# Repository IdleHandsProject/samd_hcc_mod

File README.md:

# SAMD21 HCC Module

Check out the Kickstarter for the HCC Module!

[HCC Mod Kickstarter](https://www.kickstarter.com/projects/idlehandsdev/hcc-mod-ready-to-solder-arduino-module)

An easy to solder Arduino and CircuitPython compatible surface mount module aimed to bridge the gap between using "off the shelf" microcontrollers to creating custom PCBs. 
The module will come with a standard USB enabled Arduino bootloader.

## Arduino IDE Install

Inside of the folder "BOOTLOADER" there is a folder called "IdleHandsDev". Once you download or clone the repo, take the IdleHandsDev folder and place it in the "hardware" folder found within your default Arduino folder. This will allow you to select the HCC Module in the Arduino IDE. You can also use "Arduino/Genuino Zero (Native USB). It will have the same pinout.

## Videos

## Demo Boards

### Cherry MX Board

### MOD_BOY - Arduino Gaming Device and Gaming Controller

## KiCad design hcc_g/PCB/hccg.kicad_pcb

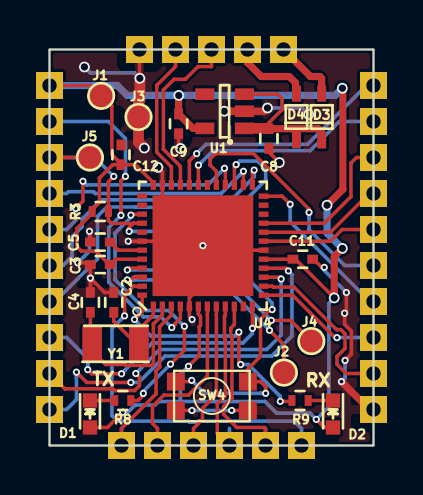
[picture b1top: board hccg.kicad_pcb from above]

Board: 2 copper layers, 18.0 x 22.0 mm, 25 parts (0 on the bottom side), 40 nets.

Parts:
C2, C4: 15pF; C_0402
C3, C5, C11, C12: 0.1uF; C_0402
C8, C9: 1uF; C_0402
D1: GLED; LED-0603
D2: YLED; LED-0603
D3, D4: BAT20J; SOD-323
J1, J2, J3, J4, J5: TEST_1P; TESTP_1_5
R3: 10k; R_0402
R8, R9: 1k; R_0402
SW4: SW_PUSH; switch_kmr2
U1: AP2112K-3.3V; SOT-23-5
U2: SAMD21G18; QFN-48-EP-ST_NoVia
U4: SAMD21_MOD; SAMD21G18_MOD
Y1: Crystal_Small; crystal_smd_3.20x1.50mm2

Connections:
+3V3: C3.1, C9.1, C11.1, C12.1, D1.2, D2.2, J1.1, R3.1, U1.5, U2.6, U2.17, U2.36, U2.44, U4.1
+BATT: D3.2, U4.27
A0/DAC: U2.3, U4.11
A1: U2.7, U4.12
A2: U2.8, U4.13
A3: U2.9, U4.14
A4: U2.10, U4.15
A5: U2.47, U4.16
AREF: U2.4, U4.2
CLK: U2.20, U4.23
D3: U2.14, U4.18
D4: U2.13, U4.19
D5: U2.24, U4.20
D6: U2.29, U4.21
D9: U2.12, U4.8
D10: U2.27, U4.7
D11: U2.25, U4.6
D12: U2.28, U4.5
D13: U2.26, U4.4
GND: C2.2, C3.2, C4.2, C5.2, C8.2, C9.2, C11.2, C12.2, J3.1, SW4.2, U1.2, U2.5, U2.18, U2.35, U2.42, U4.17, U4.31
MISO: U2.21, U4.24
MOSI: U2.19, U4.22
unnamed: C2.1, U2.1, Y1.2
unnamed: C4.1, U2.2, Y1.1
unnamed: C5.1, U2.43
unnamed: C8.1, D3.1, D4.1, U1.1, U1.3
unnamed: D1.1, R8.2
unnamed: D2.1, R9.2
RESET: J5.1, R3.2, SW4.1, U2.40, U4.3
RX/D0: U2.16, U4.10
RXLED: R9.1, U2.48
SCL: U2.32, U4.26
SDA: U2.31, U4.25
SWCLK: J4.1, U2.45
SWDIO: J2.1, U2.46
TX/D1: U2.15, U4.9
TXLED: R8.1, U2.39
USB_D+: U2.34, U4.30
USB_D-: U2.33, U4.29
VBUS: D4.2, U4.28

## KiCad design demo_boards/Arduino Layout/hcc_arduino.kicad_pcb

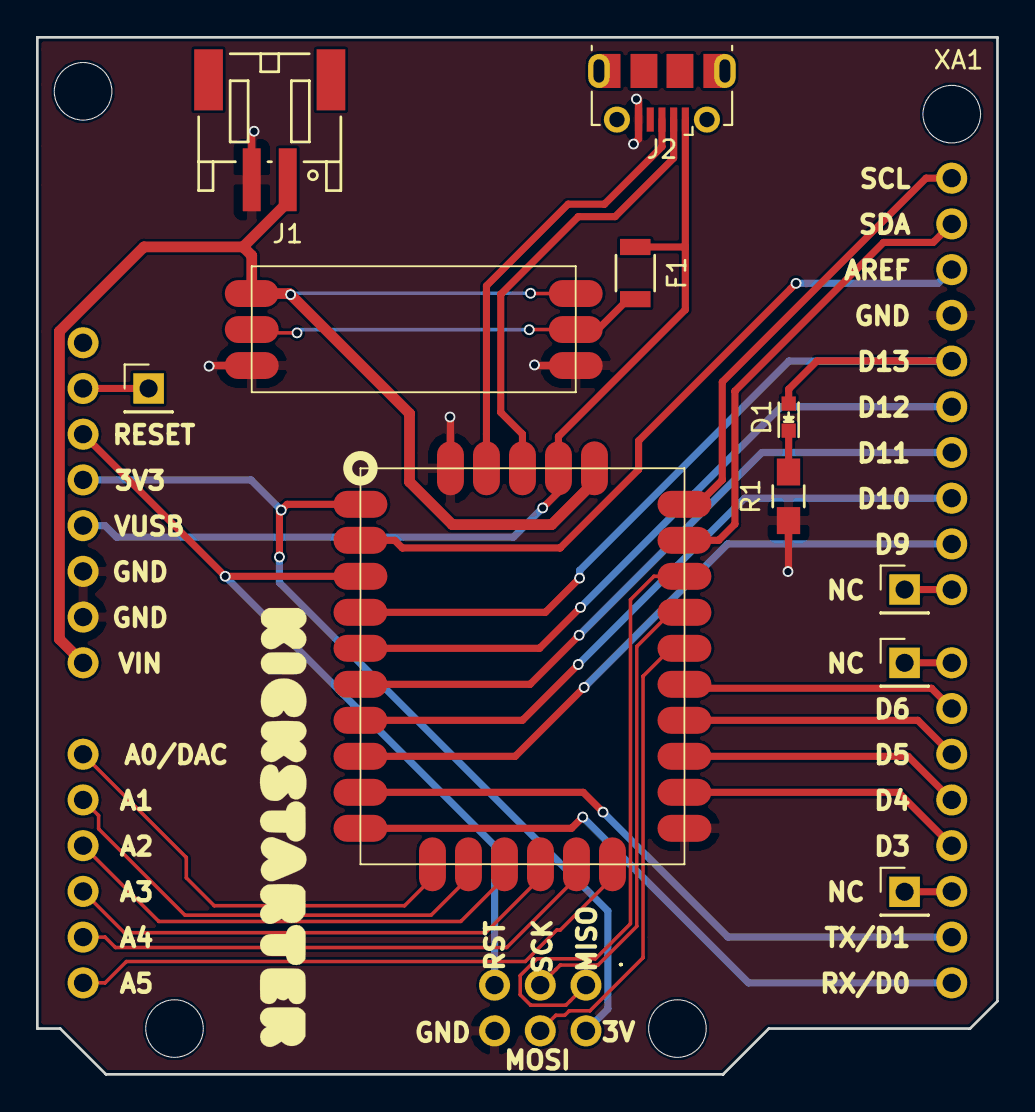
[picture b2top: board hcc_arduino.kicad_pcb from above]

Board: 2 copper layers, 53.3 x 57.6 mm, 12 parts (0 on the bottom side), 36 nets.

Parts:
D1: LED; LED-0603
F1: Fuse; R_1206
J1: BATT; Connectors_JST_S2B-PH-SM4-TB
J2: USB_OTG; USB_Micro-B_Molex-105017-0001
J3: D2; Pin_Header_Straight_1x01_Pitch2.54mm
J4: D7; Pin_Header_Straight_1x01_Pitch2.54mm
J5: D8; Pin_Header_Straight_1x01_Pitch2.54mm
J6: IOREF; Pin_Header_Straight_1x01_Pitch2.54mm
R1: 2k; R_0805_HandSoldering
U1: SAMD21_MOD; SAMD_HCC_G_FOOT
U2: charge_mod; LIPO_CHARGE_MOD_FOOTPRINT
XA1: Arduino_M0_Shield; Arduino_HCC

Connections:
+3V3: U1.1, XA1.3V3, XA1.5V2
+BATT: J1.1, U1.27, U2.1, XA1.VIN
A0/DAC: U1.11, XA1.A0
A1: U1.12, XA1.A1
A2: U1.13, XA1.A2
A3: U1.14, XA1.A3
A4: U1.15, XA1.A4
A5: U1.16, XA1.A5
AREF: U1.2, XA1.AREF
CLK: U1.23, XA1.SCK
D3: U1.18, XA1.D3
D4: U1.19, XA1.D4
D5: U1.20, XA1.D5
D6: U1.21, XA1.D6
D9: U1.8, XA1.D9
D10: U1.7, XA1.D10
D11: U1.6, XA1.D11
D12: U1.5, XA1.D12
D13: D1.2, U1.4, XA1.D13
GND: J1.2, J2.5, R1.1, U1.17, U1.31, U2.3, XA1.GND1, XA1.GND2, XA1.GND3, XA1.GND4
MISO: U1.24, XA1.MISO
MOSI: U1.22, XA1.MOSI
unnamed: D1.1, R1.2
unnamed: F1.2, U2.2
unnamed: J2.2, U1.29
unnamed: J2.3, U1.30
unnamed: J3.1, XA1.D2
unnamed: J4.1, XA1.D7
unnamed: J5.1, XA1.D8
unnamed: J6.1, XA1.IORF
RESET: U1.3, XA1.RST1, XA1.RST2
RX/D0: U1.10, XA1.D0
SCL: U1.26, XA1.SCL
SDA: U1.25, XA1.SDA
TX/D1: U1.9, XA1.D1
VBUS: F1.1, J2.1, U1.28, XA1.5V1

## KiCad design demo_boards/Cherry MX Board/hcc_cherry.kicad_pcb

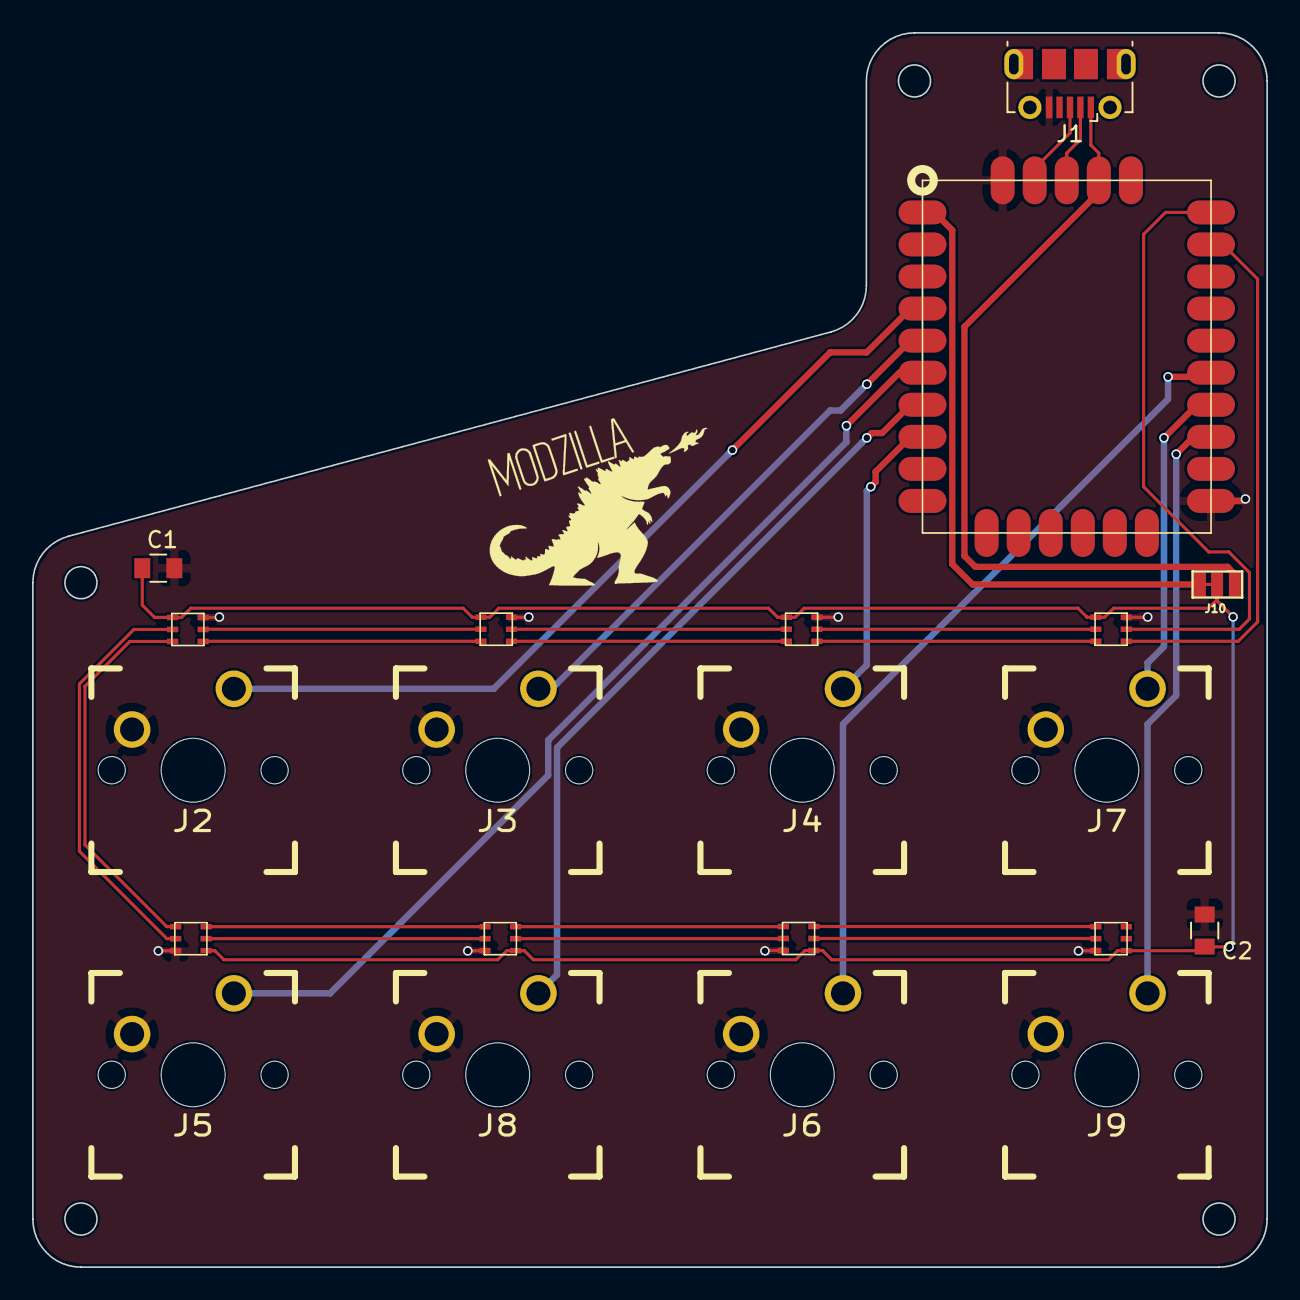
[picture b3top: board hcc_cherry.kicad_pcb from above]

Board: 2 copper layers, 77.0 x 77.0 mm, 21 parts (0 on the bottom side), 29 nets.

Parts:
C1, C2: 1uF; C_0805
J1: USB_OTG; USB_Micro-B_Molex-105017-0001
J2: SW1; CHERRY_PCB_100H
J3: SW2; CHERRY_PCB_100H
J4: SW3; CHERRY_PCB_100H
J5: SW4; CHERRY_PCB_100H
J6: SW5; CHERRY_PCB_100H
J7: SW6; CHERRY_PCB_100H
J8: SW7; CHERRY_PCB_100H
J9: SW8; CHERRY_PCB_100H
J10: GS3; 3WAY_JUMPER_SMD
U1, U2, U3, U5, U6, U7, U8, U9: APA102; APA102-2020_AFSTYLE
U4: SAMD21_MOD; SAMD_HCC_G_FOOT

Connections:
+3V3: C1.1, C2.1, J10.2, J10.3, U1.1, U2.1, U3.1, U4.1, U5.1, U6.1, U7.1, U8.1, U9.1
CKI: U1.5, U4.26
D4: J9.1, U4.19
D5: J7.1, U4.20
D6: J6.1, U4.21
D9: J4.1, U4.8
D10: J8.1, U4.7
D11: J5.1, U4.6
D12: J3.1, U4.5
D13: J2.1, U4.4
GND: C1.2, C2.2, J1.5, J2.2, J3.2, J4.2, J5.2, J6.2, J7.2, J8.2, J9.2, U1.6, U2.6, U3.6, U4.17, U4.31, U5.6, U6.6, U7.6, U8.6, U9.6
unnamed: J1.2, U4.29
unnamed: J1.3, U4.30
unnamed: U1.2, U2.5
unnamed: U1.3, U2.4
unnamed: U2.2, U3.5
unnamed: U2.3, U3.4
unnamed: U3.2, U5.5
unnamed: U3.3, U5.4
unnamed: U5.2, U6.5
unnamed: U5.3, U6.4
unnamed: U6.2, U7.5
unnamed: U6.3, U7.4
unnamed: U7.2, U8.5
unnamed: U7.3, U8.4
unnamed: U8.2, U9.5
unnamed: U8.3, U9.4
SDI: U1.4, U4.25
VBUS: J1.1, J10.1, U4.28

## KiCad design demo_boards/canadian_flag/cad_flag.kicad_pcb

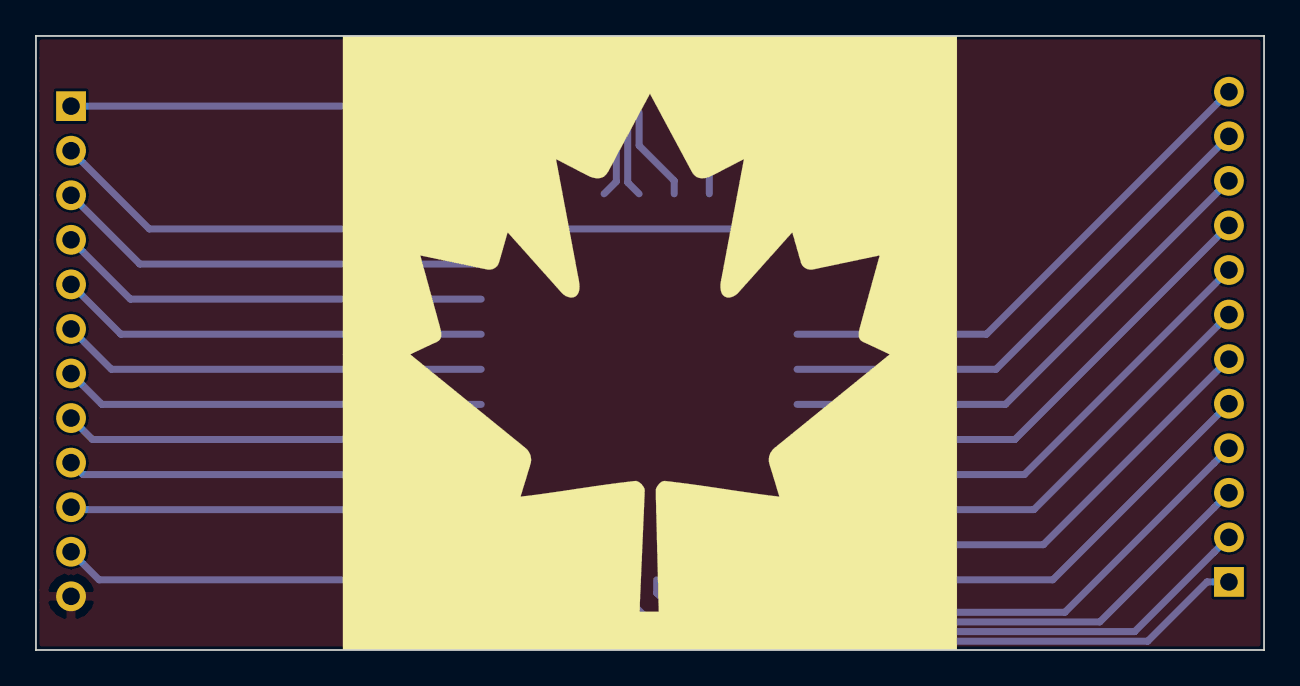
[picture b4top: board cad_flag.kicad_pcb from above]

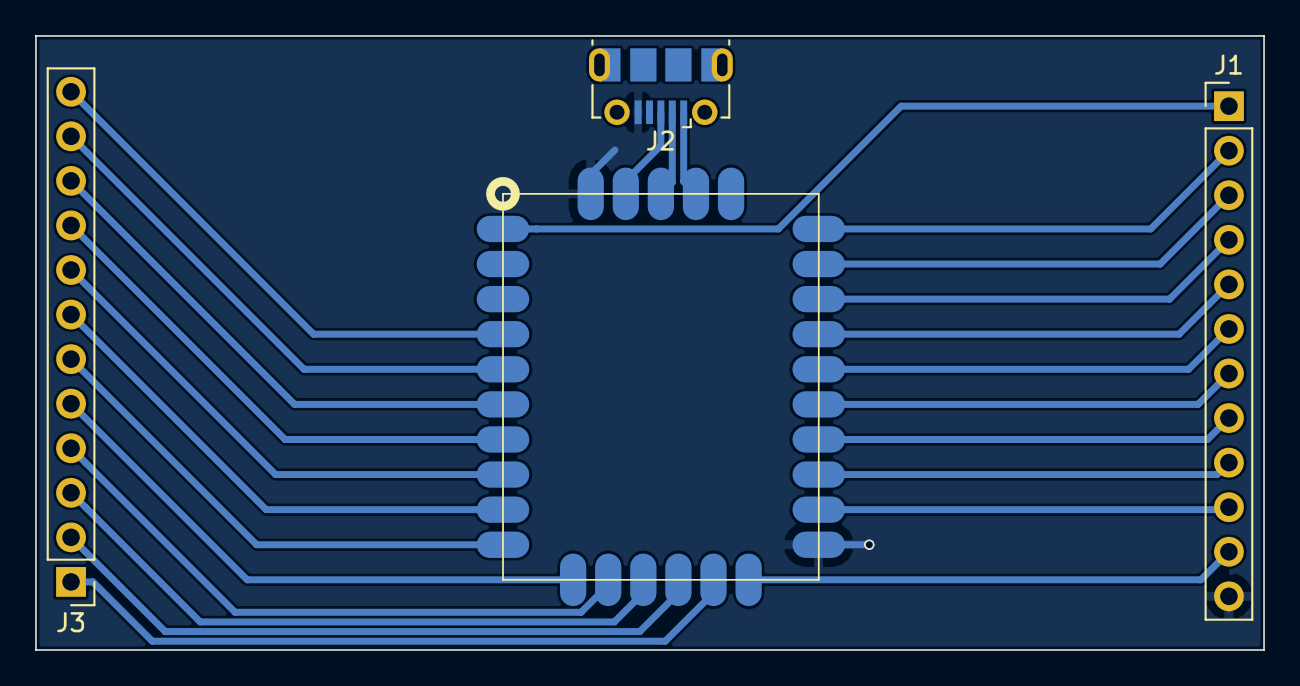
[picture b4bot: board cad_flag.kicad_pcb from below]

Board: 2 copper layers, 70.0 x 35.0 mm, 4 parts (4 on the bottom side), 27 nets.

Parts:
J1, J3: Conn_01x12; Pin_Header_Straight_1x12_Pitch2.54mm
J2: USB_OTG; USB_Micro-B_Molex-105017-0001
U1: SAMD21_MOD; SAMD_HCC_G_FOOT

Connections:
+3V3: J1.1, U1.1
A0/DAC: J3.5, U1.11
A1: J3.4, U1.12
A2: J3.3, U1.13
A3: J3.2, U1.14
A4: J3.1, U1.15
A5: J1.11, U1.16
CLK: J1.5, U1.23
D3: J1.10, U1.18
D4: J1.9, U1.19
D5: J1.8, U1.20
D6: J1.7, U1.21
D9: J3.8, U1.8
D10: J3.9, U1.7
D11: J3.10, U1.6
D12: J3.11, U1.5
D13: J3.12, U1.4
GND: J1.12, J2.5, U1.17, U1.31
MISO: J1.4, U1.24
MOSI: J1.6, U1.22
unnamed: J2.1, U1.28
unnamed: J2.2, U1.29
unnamed: J2.3, U1.30
RX/D0: J3.6, U1.10
SCL: J1.2, U1.26
SDA: J1.3, U1.25
TX/D1: J3.7, U1.9

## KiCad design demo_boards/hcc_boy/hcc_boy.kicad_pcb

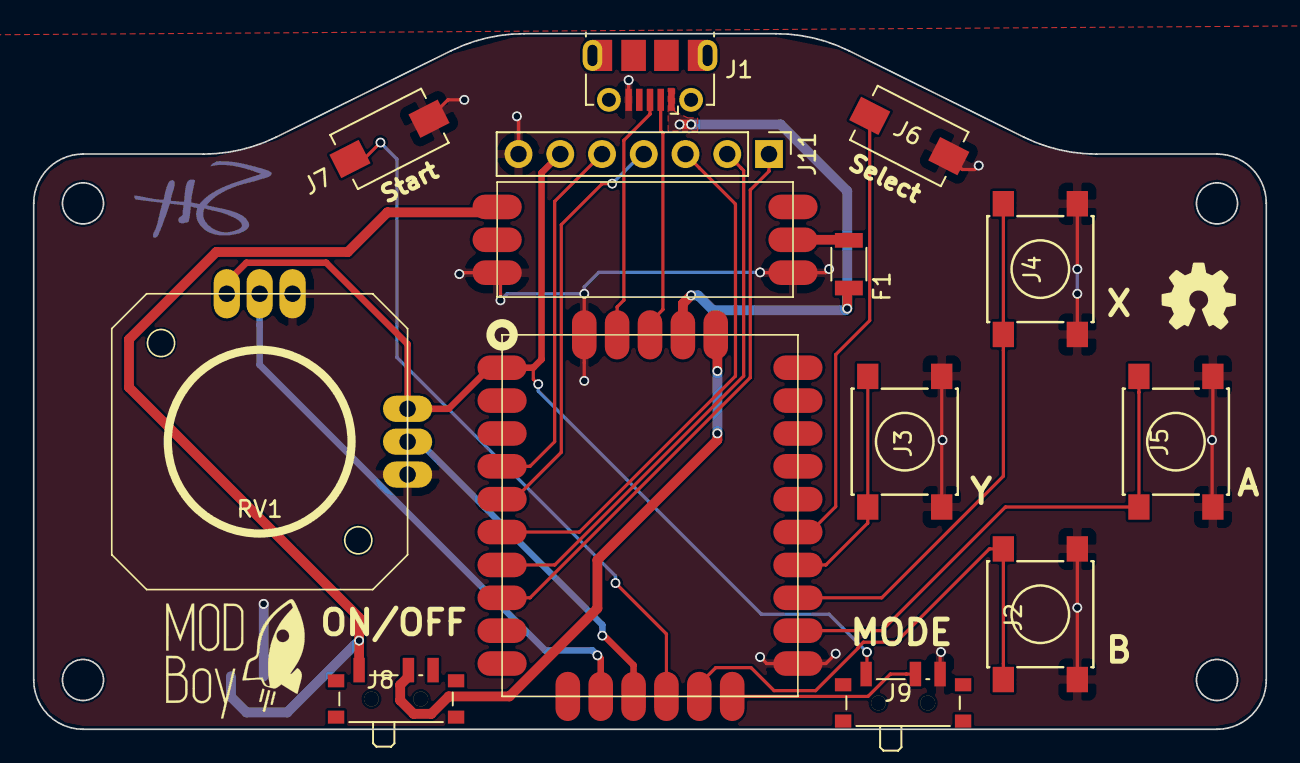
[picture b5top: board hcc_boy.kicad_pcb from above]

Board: 2 copper layers, 75.0 x 42.3 mm, 15 parts (1 on the bottom side), 22 nets.

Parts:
BT1: Battery_Cell; Connectors_JST_S2B-PH-SM4-TB
F1: Fuse; R_1206
J1: USB_OTG; USB_Micro-B_Molex-105017-0001
J2: A; SW_SPST_PTS645
J3: B; SW_SPST_PTS645
J4: X; SW_SPST_PTS645
J5: Y; SW_SPST_PTS645
J6: Start; SW_SPST_EVQPE1
J7: Select; SW_SPST_EVQPE1
J8: PWR; SW_SPDT_PCM12
J9: Selector; SW_SPDT_PCM12
J11: OLED; Pin_Header_Straight_1x07_Pitch2.54mm
RV1: JOYSTICK; JOYSTICK_MINI_2AXIS
U1: charge_mod; LIPO_CHARGE_MOD_FOOTPRINT
U4: SAMD21_MOD; SAMD_HCC_G_FOOT

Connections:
+3V3: J9.1, J11.6, RV1.3, RV1.6, U4.1
+BATT: BT1.1, J8.1, U1.1
A1: RV1.5, U4.12
A2: RV1.2, U4.13
A3: J7.1, U4.14
A4: J2.1, U4.15
A5: J9.2, U4.16
D3: J5.1, U4.18
D4: J4.1, U4.19
D5: J3.1, U4.20
D6: J6.1, U4.21
D9: J11.1, U4.8
D10: J11.2, U4.7
D11: J11.3, U4.6
D12: J11.4, U4.5
D13: J11.5, U4.4
GND: BT1.2, J1.5, J2.2, J3.2, J4.2, J5.2, J6.2, J7.2, J9.3, J11.7, RV1.1, RV1.4, U1.3, U4.17, U4.31
unnamed: F1.2, U1.2
unnamed: J1.2, U4.29
unnamed: J1.3, U4.30
unnamed: J8.2, U4.27
VBUS: F1.1, J1.1, U4.28

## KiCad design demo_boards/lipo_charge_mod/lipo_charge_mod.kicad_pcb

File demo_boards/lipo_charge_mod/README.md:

# Sensory_Adaptation_Bot
A Neural network robot for learning new sensors without programming them specifically.

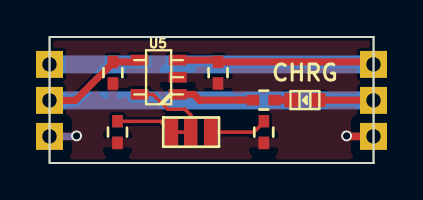
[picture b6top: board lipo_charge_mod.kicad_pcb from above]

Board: 2 copper layers, 18.0 x 7.0 mm, 9 parts (0 on the bottom side), 7 nets.

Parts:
C7, C10: 4.7uF; C_0402_Hand
D6: CHRG; Led_0603
J1: GS3; 3WAY_JUMPER_SMD
J2: Conn_01x06; LIPO_CHARGE_MOD
R1: 0; R_0402_Hand
R5: 33k; R_0402_Hand
R14: 1K; R_0402_Hand
U5: MCP73831T; sot23-5

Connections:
GND: C7.2, C10.2, J2.3, J2.6, R1.1, R5.1, U5.2
unnamed: D6.1, R14.2
unnamed: J1.1, R1.2
unnamed: J1.2, J1.3, R5.2, U5.5
unnamed: R14.1, U5.1
VBATT: C10.1, J2.1, J2.4, U5.3
VCC: C7.1, D6.2, J2.2, J2.5, U5.4

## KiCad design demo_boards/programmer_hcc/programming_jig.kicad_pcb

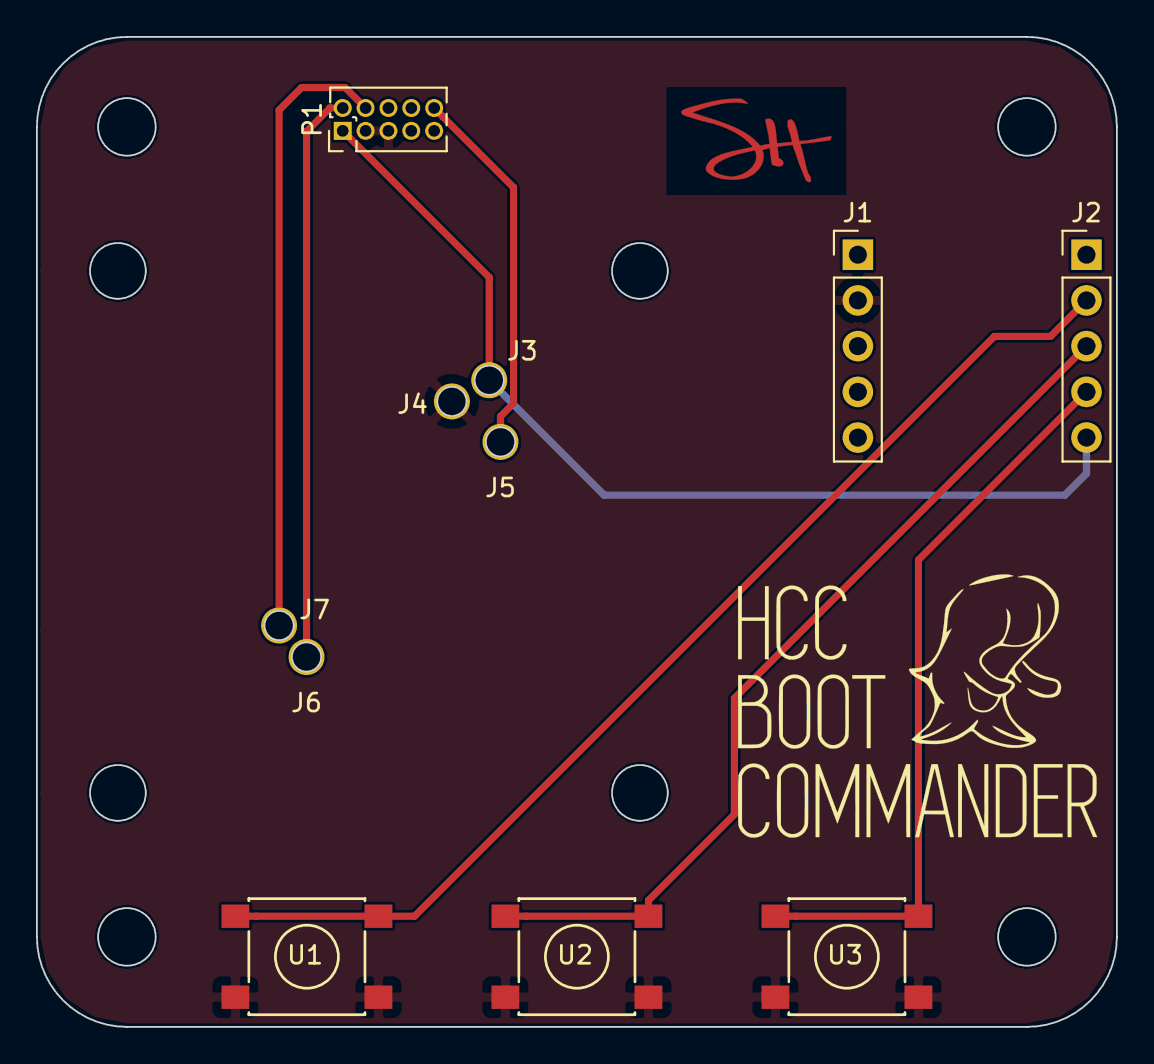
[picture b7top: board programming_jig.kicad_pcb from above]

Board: 2 copper layers, 60.0 x 55.0 mm, 11 parts (0 on the bottom side), 8 nets.

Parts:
J1: Trinket_Left; Pin_Header_Straight_1x05_Pitch2.54mm
J2: Trinket_Right; Pin_Header_Straight_1x05_Pitch2.54mm
J3: 3V3; POGO_PIN
J4: GND; POGO_PIN
J5: RST; POGO_PIN
J6: SWDIO; POGO_PIN
J7: SWCLK; POGO_PIN
P1: DBG_CONN; Pin_Header_Straight_2x05_Pitch1.27mm
U1: SW1; SW_SPST_PTS645
U2: SW2; SW_SPST_PTS645
U3: SW3; SW_SPST_PTS645

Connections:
0: J2.2, U1.1
1: J2.3, U2.1
2: J2.4, U3.1
+3V3: J2.5, J3.1, P1.1
GND: J1.2, J4.1, P1.3, P1.5, U1.2, U2.2, U3.2
RST: J5.1, P1.10
SWCLK: J7.1, P1.4
SWDIO: J6.1, P1.2

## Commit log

2018-05-24 corrected README
2018-06-23 Boards ordered wth gerbs
2018-06-23 restructure folders and rename
2018-06-30 changes to filenames and folder system
2018-07-19 added demo boards
2018-07-19 added logos, changed regulator to ap2112
2018-07-19 Fixed USB Ground
2018-07-19 fixed battery connection on HCC_Boy
2018-07-19 fixed usb connector
2018-07-19 fixed hcc breakout board, added lipo charger
2018-07-26 updated hcc mod and modzilla board gerbs
2018-07-26 connected 3V3 to LEDs without needing jumper
2018-07-30 cleaned up libs, removed libs from project files, removed unused footprints
2018-07-31 added Arduino Example Code Folder and files
2018-07-31 updated Readme with MODBOY video
2018-08-08 added boot commander firmware and bootloader
2018-10-29 new VID/PID
2018-10-29 old bootloader
2018-10-29 added footprints
2018-10-29 small changes
2018-11-13 Updated VID/PID
2018-11-14 added hardware folder and bootloader compilier
2018-11-14 updated ignore file
2018-11-14 updated hardware folder
